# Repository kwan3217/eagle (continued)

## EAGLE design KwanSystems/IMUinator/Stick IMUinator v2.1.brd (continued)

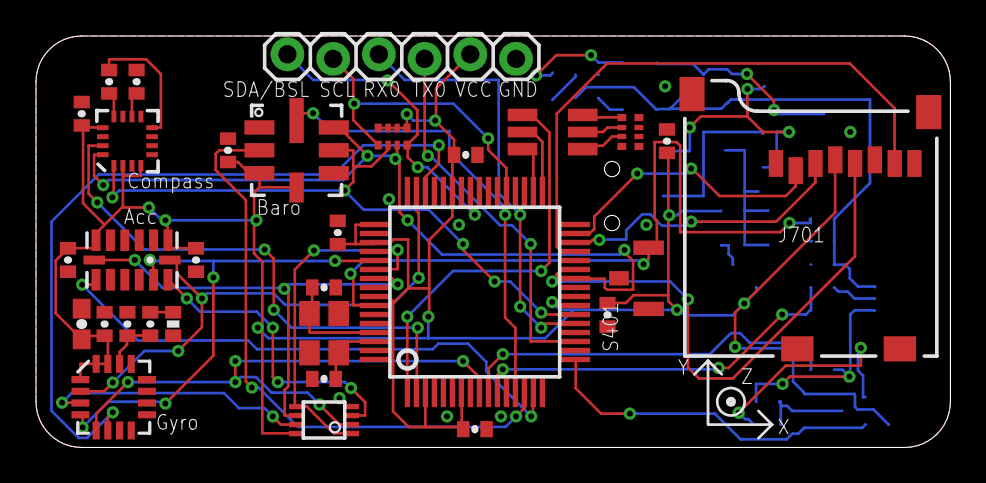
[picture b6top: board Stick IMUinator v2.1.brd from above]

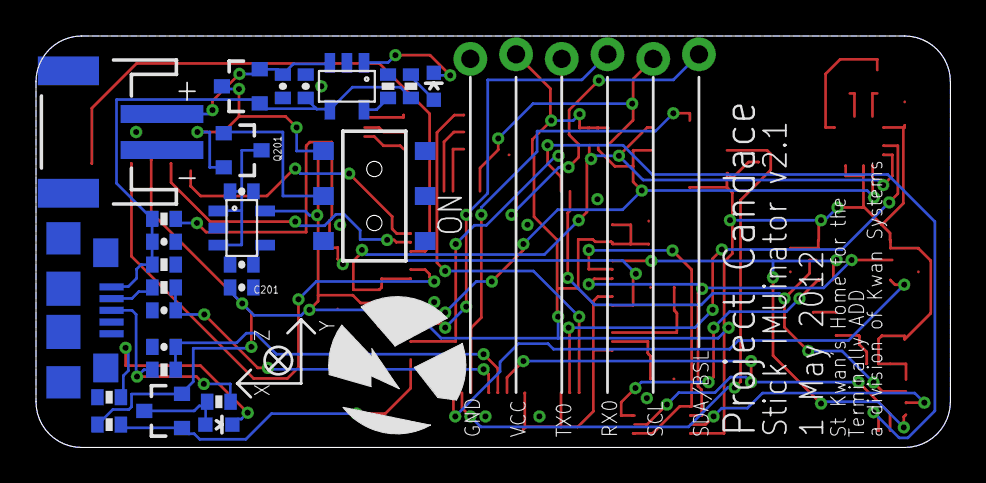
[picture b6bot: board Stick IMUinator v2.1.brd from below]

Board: 2 copper layers, 50.8 x 22.9 mm, 59 parts (28 on the bottom side), 54 nets.

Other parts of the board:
U$1: KWAN_CIRCLE
